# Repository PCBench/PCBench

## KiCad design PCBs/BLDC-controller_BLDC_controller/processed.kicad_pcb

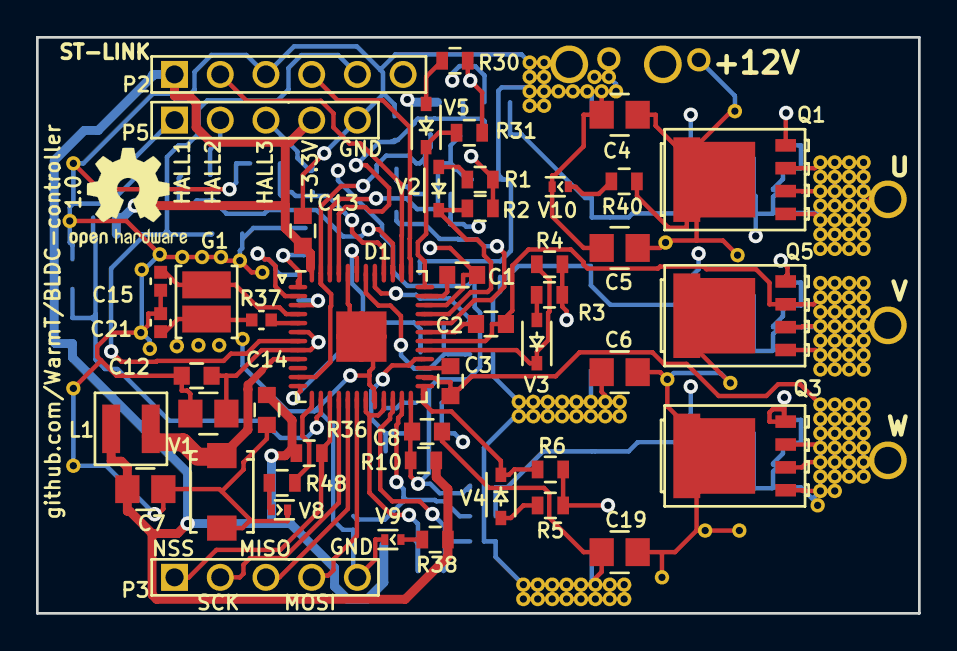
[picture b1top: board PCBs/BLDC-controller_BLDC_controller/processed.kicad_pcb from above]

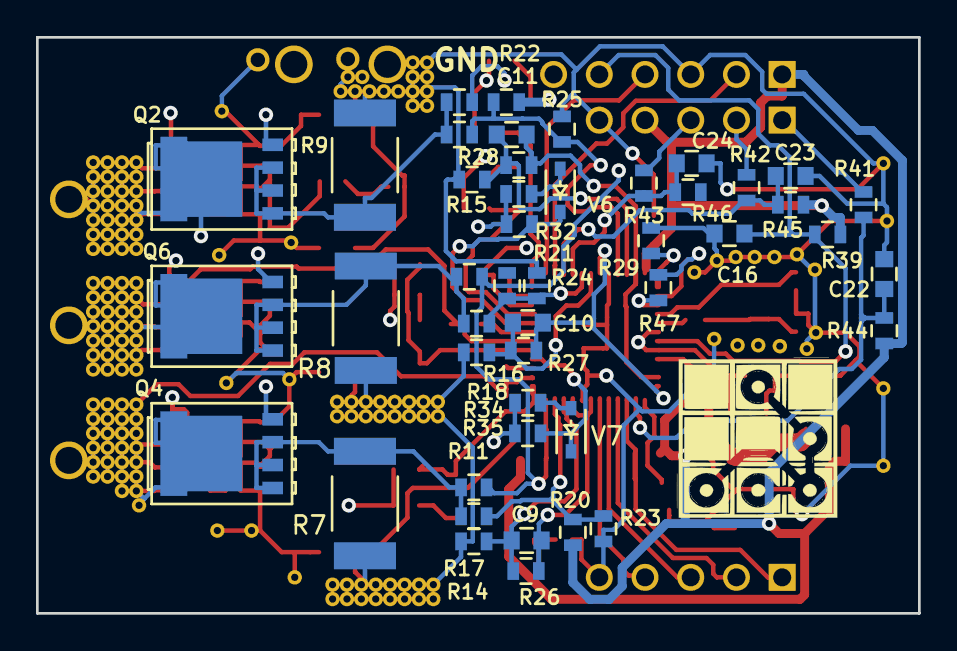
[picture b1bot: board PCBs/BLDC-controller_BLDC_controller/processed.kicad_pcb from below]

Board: 4 copper layers, 49.0 x 32.0 mm, 92 parts (46 on the bottom side), 64 nets.

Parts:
C1, C2, C3, C12, C13, C14: 100n; C_0603
C4, C5, C6, C17, C19: 220n; C_0805
C7: 47u; C_0805
C8: 1n0; C_0603
C9, C10, C11: 100p; C_0603
C15, C21: 10p; C_0402
C16: 3n3; C_0603
C22, C23, C24: 10p; C_0603
D1: STSPIN32F0; QFN-48-1EP_7x7mm_Pitch0.5mm
G1: NX3225GD; Crystal_3225
L1: SRN3015-220M; BOURNS-SRN3015
P2: CONN_01X06; PINHEAD1-6
P3, P5: CONN_01X05; PINHEAD1-5
Q1, Q2, Q3, Q4, Q5, Q6: PSMN2R0-30YLD; SOT-669_LFPAK56
R1, R3, R5, R30, R32, R34, R47: 10R; R_0603
R2, R4, R6, R31, R33, R35: 62R; R_0603
R7, R8, R9: 0R01; R_2512
R10: 46k4; R_0603
R11, R12, R13, R29, R36, R40: 2k2; R_0603
R14, R15, R16, R41, R42, R43: 1k0; R_0603
R17, R18, R19, R23, R24, R25, R48: 560R; R_0603
R20, R21, R22: 8k2; R_0603
R26, R27, R28: 15k; R_0603
R37: 10R; R_0402_MOST
R38: 330R; R_0603
R39: 39k; R_0603
R44, R45, R46: 10k; R_0603
V1: STPS1L60A; SMA
V2, V3, V4, V5, V6, V7: 4148WS; SOD-323
V8, V9, V10: LED_ALT; LED_0402

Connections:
+3V3: C7.1, C13.1, C14.1, D1.48, L1.1, P2.1, P5.4, R10.2, R20.1, R22.1, R36.1, R38.1, R39.1, R44.1, R45.1
+12V: C4.1, C5.1, C6.1, C12.1, C17.1, C19.1, D1.6, D1.8, Q1.5, Q3.5, Q5.5, R40.1
/HALL1/A+: C22.1, D1.14, R41.1, R44.2
/HALL2/B+: C23.1, D1.39, R42.1, R45.2
/HALL3/Z+: C24.1, D1.40, R43.1, R46.2
/HSU: Q1.4, R1.1, R2.1
/HSV: Q5.4, R3.1, R4.1
/HSW: Q3.4, R5.1, R6.1
/LSU: Q2.4, R30.1, R31.1
/LSV: Q6.4, R32.1, R33.1
/LSW: Q4.4, R34.1, R35.1
/NRST: C16.1, D1.7, P2.5, R39.2
/OC_COMP: C8.1, D1.24, R10.1, R11.2, R12.2, R13.2
/OP1N: C9.2, D1.22, R14.2, R26.2
/OP1P: D1.23, R17.1, R20.2, R23.1
/OP2N: C10.2, D1.42, R16.2, R27.2
/OP2P: D1.41, R18.1, R21.2, R24.1
/OP3N: C11.2, D1.46, R15.2, R28.2
/OP3P: D1.45, R19.1, R22.2, R25.1
/OP4N: D1.2, R47.2
/OP4P: D1.1, R29.1
/OSC_IN: C15.1, D1.4, G1.1
/OUTU: C1.1, D1.34, Q1.1, Q1.2, Q1.3, Q2.5
/OUTV: C2.1, D1.30, Q5.1, Q5.2, Q5.3, Q6.5
/OUTW: C3.1, D1.26, Q3.1, Q3.2, Q3.3, Q4.5
/PA2: D1.13, R48.1
/PA2_LED: R48.2, V8.2
/SPI1_MISO: D1.17, P3.3
/SPI1_MOSI: D1.18, P3.4
/SPI1_NSS: D1.15, P3.1, R36.2
/SPI1_SCK: D1.16, P3.2
/SW: D1.9, L1.2, V1.1
/SWCLK: D1.38, P2.2
/SWDIO: D1.37, P2.4
/U_ADC: C11.1, D1.11, D1.47, R28.1
/VBOOSTU: C1.2, D1.35
/VBOOSTV: C2.2, D1.31
/VBOOSTW: C3.2, D1.27
/V_ADC: C10.1, D1.12, D1.43, R27.1
/W_ADC: C9.1, D1.19, D1.21, R26.1
GND: C4.2, C5.2, C6.2, C7.2, C8.2, C12.2, C13.2, C14.2, C15.2, C16.2, C17.2, C19.2, C21.2, C22.2, C23.2, C24.2, D1.20, D1.44, D1.49, P2.3, P3.5, P5.5, R7.2, R8.2, R9.2, R14.1, R15.1, R16.1, R23.2, R24.2, R25.2, R29.2, V1.2, V8.1, V9.1, V10.1
unnamed: C21.1, G1.2, R37.2
unnamed: D1.3, R47.1
unnamed: D1.5, R37.1
unnamed: D1.25, R6.2, V4.1
unnamed: D1.28, R35.2, V7.1
unnamed: D1.29, R4.2, V3.1
unnamed: D1.32, R33.2, V6.1
unnamed: D1.33, R2.2, V2.1
unnamed: D1.36, R31.2, V5.1
unnamed: P5.1, R41.2
unnamed: P5.2, R42.2
unnamed: P5.3, R43.2
unnamed: R1.2, V2.2
unnamed: R3.2, V3.2
unnamed: R5.2, V4.2
unnamed: R30.2, V5.2
unnamed: R32.2, V6.2
unnamed: R34.2, V7.2
unnamed: R38.2, V9.2
unnamed: R40.2, V10.2
U_SENSE_P: Q2.1, Q2.2, Q2.3, R9.1, R13.1, R19.2
V_SENSE_P: Q6.1, Q6.2, Q6.3, R8.1, R12.1, R18.2
W_SENSE_P: Q4.1, Q4.2, Q4.3, R7.1, R11.1, R17.2

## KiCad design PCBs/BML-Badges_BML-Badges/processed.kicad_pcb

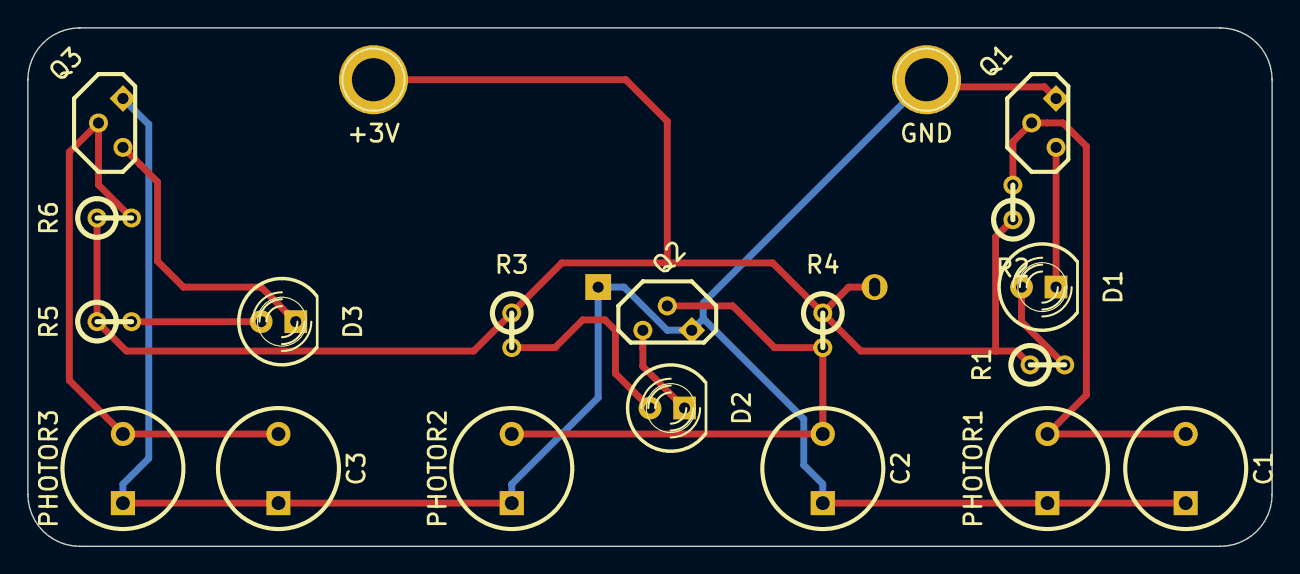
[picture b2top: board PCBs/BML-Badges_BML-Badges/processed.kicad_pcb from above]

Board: 2 copper layers, 91.4 x 38.1 mm, 21 parts (1 on the bottom side), 11 nets.

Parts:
BT1: 3V; BS-7-CR2032-2
C1, C2, C3: 22uF; C2V8
D1, D2, D3: LED; LED-5MM
P1: +3V; 1pin
P2: GND; 1pin
PHOTOR1, PHOTOR2, PHOTOR3: PHOTOR; LDR
Q1, Q2, Q3: PN2222A; TO92-EBC-num
R1, R3, R5: 330; R1
R2, R4, R6: 100k; R1

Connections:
3V: BT1.1, P1.1, R1.1, R2.1, R3.1, R4.1, R5.1, R6.1
GND: BT1.2, C1.2, C2.2, C3.2, P2.1, PHOTOR1.2, PHOTOR2.2, PHOTOR3.2, Q1.1, Q2.1, Q3.1
unnamed: C1.1, PHOTOR1.1, Q1.2, R2.2
unnamed: C2.1, PHOTOR2.1, Q2.2, R4.2
unnamed: C3.1, PHOTOR3.1, Q3.2, R6.2
unnamed: D1.1, R1.2
unnamed: D1.2, Q1.3
unnamed: D2.1, R3.2
unnamed: D2.2, Q2.3
unnamed: D3.1, R5.2
unnamed: D3.2, Q3.3

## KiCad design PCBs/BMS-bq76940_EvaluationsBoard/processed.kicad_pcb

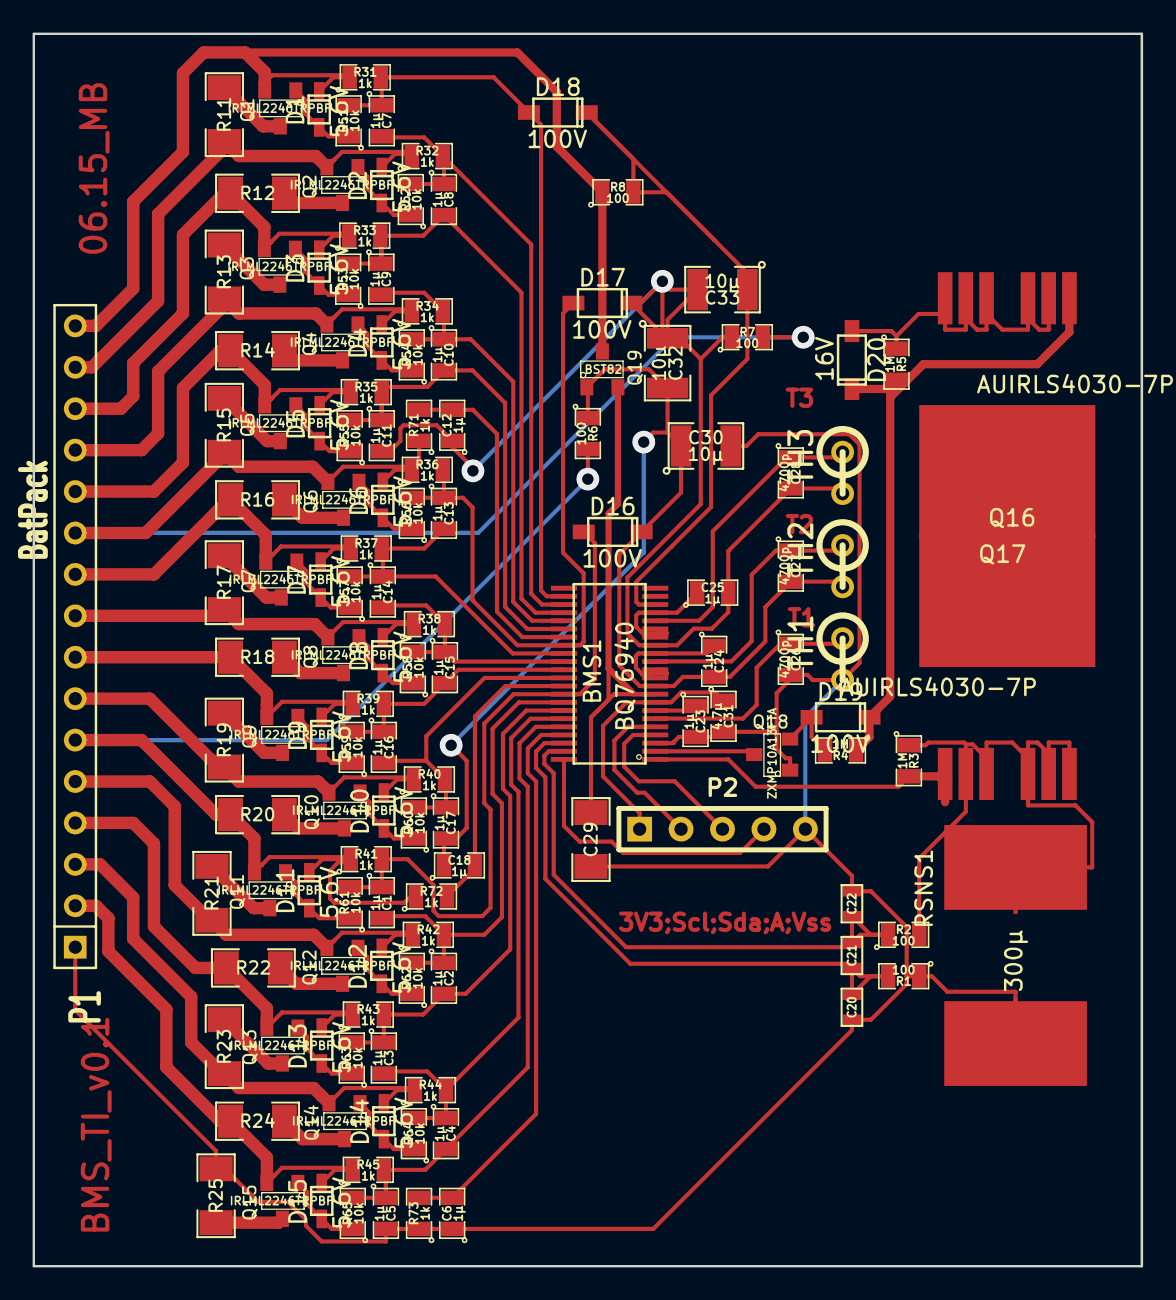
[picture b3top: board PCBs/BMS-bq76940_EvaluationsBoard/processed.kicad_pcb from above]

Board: 2 copper layers, 67.9 x 75.6 mm, 134 parts (0 on the bottom side), 87 nets.

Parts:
BMS1: BQ76940
C1, C2, C3, C4, C5, C6, C7, C8, C9, C10, C11, C12, C13, C14, C15, C16, C17, C18, C23, C24, C25: 1µ; SM0805
C20, C21, C22: 0.1µ; SM0603
C26, C27, C28: 4700p; SM0805
C29: 1µ; SM1206
C30, C32, C33: 10µ; SM1210
C31: 4.7µ; SM0805
D1, D2, D3, D4, D5, D6, D7, D8, D9, D10, D11, D12, D13, D14, D15: 5.6V; SOD323
D16, D17, D18, D19: 100V; SOD123
D20: 16V; SOD123
P1: BatPack; SIL-16
P2: µC; PIN_ARRAY_5x1
Q1, Q2, Q3, Q4, Q5, Q6, Q7, Q8, Q9, Q10, Q11, Q12, Q13, Q14, Q15: IRLML2246TRPBF; SOT23
Q16, Q17: AUIRLS4030-7P
Q18: ZXMP10A13FTA; SOT23
Q19: BST82; SOT23
R1, R2, R6, R7, R8: 100; SM0805
R3, R4, R5: 1M; SM0805
R11, R12, R13, R14, R15, R16, R17, R18, R19, R20, R21, R22, R23, R24, R25: 39; SM1206
R31, R32, R33, R34, R35, R36, R37, R38, R39, R40, R41, R42, R43, R44, R45, R71, R72, R73: 1k; SM0805
R51, R52, R53, R54, R55, R56, R57, R58, R59, R60, R61, R62, R63, R64, R65: 10k; SM0805
RSNS1: 300µ; WSLP5931
TH1, TH2, TH3: THERMISTOR; R1

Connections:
/BatPack/C1: D15.2, P1.2, Q15.2, R24.1, R45.1
/BatPack/C2: D14.2, P1.3, Q14.2, R23.1, R44.1
/BatPack/C3: D13.2, P1.4, Q13.2, R22.1, R43.1
/BatPack/C4: D12.2, P1.5, Q12.2, R21.1, R42.1
/BatPack/C6: D10.2, P1.7, Q10.2, R19.1, R40.1
/BatPack/C7: D9.2, P1.8, Q9.2, R18.1, R39.1
/BatPack/C8: D8.2, P1.9, Q8.2, R17.1, R38.1
/BatPack/C9: D7.2, P1.10, Q7.2, R16.1, R37.1
/BatPack/C11: D5.2, P1.12, Q5.2, R14.1, R35.1
/BatPack/C12: D4.2, P1.13, Q4.2, R13.1, R34.1
/BatPack/C13: D3.2, P1.14, Q3.2, R12.1, R33.1
/BatPack/C14: D2.2, P1.15, Q2.2, R11.1, R32.1
/BatPack/VC0: BMS1.41, C6.2, R73.2
/BatPack/VC1: BMS1.40, C4.2, C5.1, R45.2, R65.2
/BatPack/VC2: BMS1.39, C3.2, C4.1, R44.2, R64.2
/BatPack/VC3: BMS1.38, C2.2, C3.1, R43.2, R63.2
/BatPack/VC4: BMS1.37, C1.2, C2.1, R42.2, R62.2
/BatPack/VC5: BMS1.36, C1.1, D16.1, R41.2, R61.2
/BatPack/VC6: BMS1.34, C16.2, C17.1, R40.2, R60.2
/BatPack/VC7: BMS1.33, C15.2, C16.1, R39.2, R59.2
/BatPack/VC8: BMS1.32, C14.2, C15.1, R38.2, R58.2
/BatPack/VC9: BMS1.31, C13.2, C14.1, R37.2, R57.2
/BatPack/VC10: BMS1.30, C13.1, D17.1, R36.2, R56.2
/BatPack/VC11: BMS1.28, C10.2, C11.1, R35.2, R55.2
/BatPack/VC12: BMS1.27, C9.2, C10.1, R34.2, R54.2
/BatPack/VC13: BMS1.26, C8.2, C9.1, R33.2, R53.2
/BatPack/VC14: BMS1.25, C7.2, C8.1, R32.2, R52.2
/BatPack/VC15: BMS1.24, C7.1, D18.1, R31.2, R51.2
/COM/BAT: BMS1.20, C33.1, D18.2, R8.2
/COM/CHG: BMS1.2, Q18.3
/COM/DSC: BMS1.1, Q16.1, R3.2
/COM/REGOUT: BMS1.8, C31.1, P2.1
/COM/REGSRC: BMS1.9, C29.1, Q19.2
/COM/SCL: BMS1.5, P2.2
/COM/SDA: BMS1.4, P2.3
/COM/SRN: BMS1.43, C21.2, C22.1, R2.1
/COM/SRP: BMS1.42, C20.2, C21.1, R1.2
A: D11.2, P1.6, Q11.2, R6.2, R20.1, R41.1, R72.1
ALERT: BMS1.44, P2.4
B: D6.2, P1.11, Q6.2, R7.2, R15.1, R36.1, R71.1
unnamed: D5.1, Q5.1, R55.1
unnamed: D3.1, Q3.1, R53.1
unnamed: D4.1, Q4.1, R54.1
unnamed: D6.1, Q6.1, R56.1
unnamed: D2.1, Q2.1, R52.1
unnamed: D1.1, Q1.1, R51.1
unnamed: Q3.3, R13.2
unnamed: Q4.3, R14.2
unnamed: Q5.3, R15.2
unnamed: Q6.3, R16.2
unnamed: Q7.3, R17.2
unnamed: Q8.3, R18.2
unnamed: D9.1, Q9.1, R59.1
unnamed: Q9.3, R19.2
unnamed: D10.1, Q10.1, R60.1
unnamed: Q1.3, R11.2
unnamed: Q2.3, R12.2
unnamed: Q14.3, R24.2
unnamed: Q13.3, R23.2
unnamed: Q12.3, R22.2
unnamed: Q11.3, R21.2
unnamed: Q10.3, R20.2
unnamed: Q15.3, R25.2
unnamed: D11.1, Q11.1, R61.1
unnamed: D12.1, Q12.1, R62.1
unnamed: D14.1, Q14.1, R64.1
unnamed: D7.1, Q7.1, R57.1
unnamed: D8.1, Q8.1, R58.1
unnamed: D13.1, Q13.1, R63.1
unnamed: D15.1, Q15.1, R65.1
unnamed: BMS1.7, C23.1
unnamed: BMS1.16, BMS1.17, BMS1.19, C25.1
unnamed: BMS1.11, BMS1.12, BMS1.14, C24.1
unnamed: D19.2, D20.2, Q17.1, R4.1, R5.2
unnamed: Q16.8, Q17.8
unnamed: D19.1, Q18.2, R4.2
unnamed: Q16.2, Q16.3, Q16.5, Q16.6, Q16.7, R2.2, R3.1, RSNS1.1
PACK+: D1.2, P1.16, Q1.2, Q19.3, R8.1, R31.1
PACK-: D20.1, Q17.2, Q17.3, Q17.5, Q17.6, Q17.7, R5.1
TS1: BMS1.6, C26.1, TH1.1
TS2: BMS1.13, C27.1, TH2.1
TS3: BMS1.18, C28.1, TH3.1
VC5B: BMS1.35, C18.2, R72.2
VC5x: BMS1.10, C17.2, C18.1, C24.2, C27.2, C30.1, C32.2, D16.2, Q19.1, R6.1, TH2.2
VC10B: BMS1.29, C12.2, R71.2
VC10x: BMS1.15, C11.2, C12.1, C25.2, C28.2, C32.1, C33.2, D17.2, R7.1, TH3.2
VSS: BMS1.3, C5.2, C6.1, C20.1, C22.2, C23.2, C26.2, C29.2, C30.2, C31.2, P1.1, P2.5, Q18.1, R1.1, R25.1, R73.1, RSNS1.2, TH1.2

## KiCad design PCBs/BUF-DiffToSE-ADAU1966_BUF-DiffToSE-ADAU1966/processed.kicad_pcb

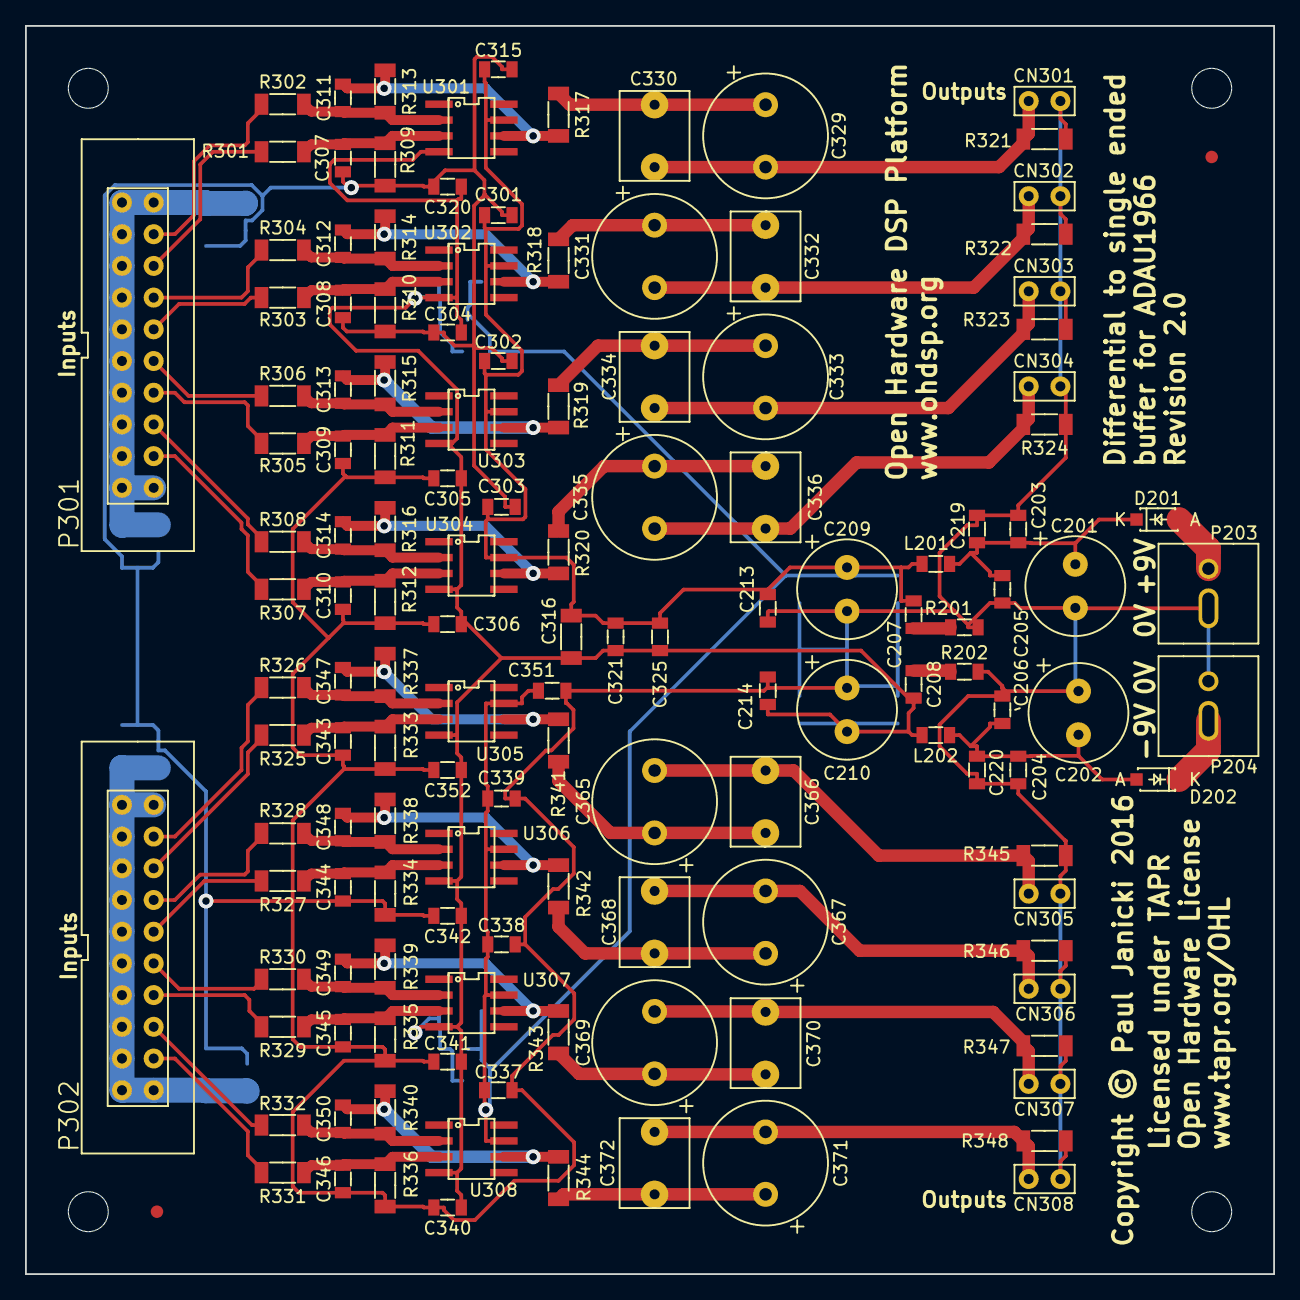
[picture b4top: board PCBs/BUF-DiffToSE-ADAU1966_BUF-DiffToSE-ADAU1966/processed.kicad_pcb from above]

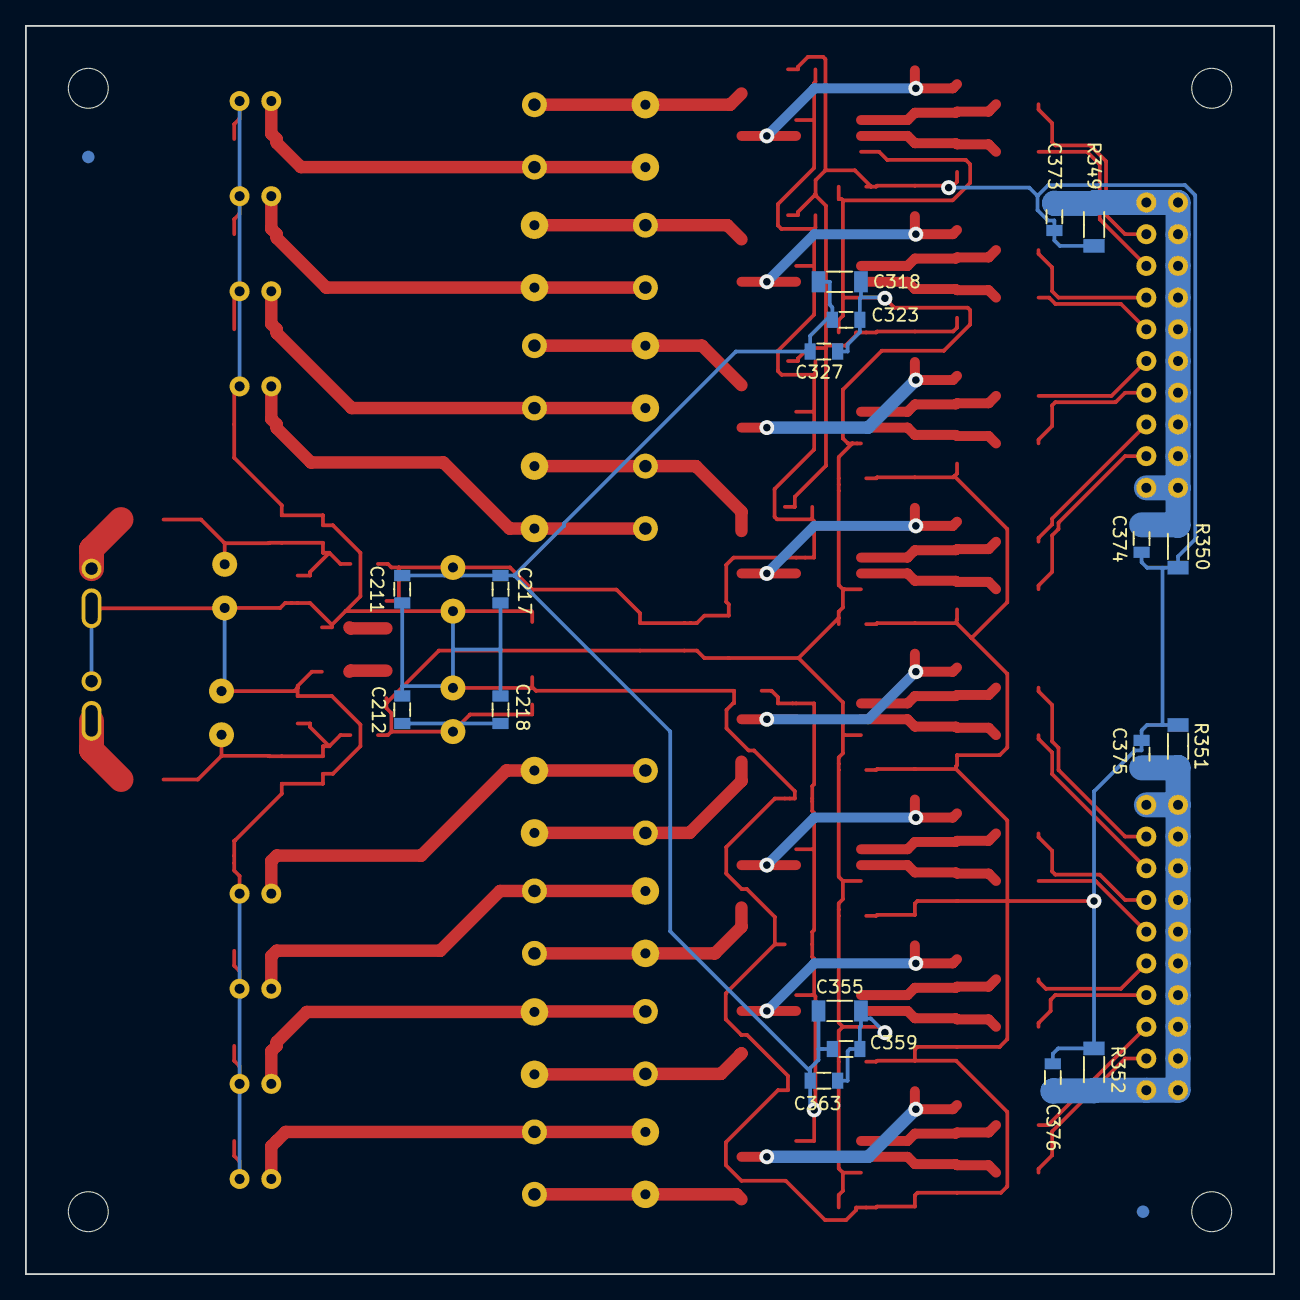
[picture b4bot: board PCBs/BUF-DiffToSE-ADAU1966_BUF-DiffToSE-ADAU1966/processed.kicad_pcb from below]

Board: 2 copper layers, 100.0 x 100.0 mm, 165 parts (20 on the bottom side), 67 nets.

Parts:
C201, C202, C209, C210: 220u; CAP-TH-D8mmP3.5mm
C203, C204, C211, C212, C301, C302, C303, C304, C305, C306, C315, C320, C321, C323, C337, C338, C339, C340, C341, C342, C351, C352, C359, C373, C374, C375, C376: 100n; SMD-0805
C205, C206, C213, C214, C325, C327, C363: 10n; SMD-0805
C207, C208: 100p; SMD-0805
C217, C218, C219, C220: 22u; SMD-0805
C307, C308, C309, C310, C311, C312, C313, C314, C343, C344, C345, C346, C347, C348, C349, C350: 1n; SMD-0805
C316, C318, C355: 10u; SMD-1206
C329, C331, C333, C335, C365, C367, C369, C371: 100u; CAP-TH-D10mmP5mm
C330, C332, C334, C336, C366, C368, C370, C372: 100n; CAP_TH_5mm
CN301, CN302, CN303, CN304, CN305, CN306, CN307, CN308: COAX; CONN_SIL_2
D201, D202: SS14L; DIODE-SOD-123
FID1, FID2, FID3, FID4: MNT_HOLE; FID-1MM-3MM
L201, L202: 600R@100MHz; SMD-0805
MNT201, MNT202, MNT203, MNT204: MNT_HOLE; MNT_HOLE_3.2mm
P203, P204: CONN_2x1; CONN-2WAY-2.54mm-3.81mm-SPACING
P301, P302: CONN_02X10; CONN_DIL_2X10_BOX
R201, R202: 47; SMD-0805
R301, R302, R303, R304, R305, R306, R307, R308, R325, R326, R327, R328, R329, R330, R331, R332: 1k3; SMD-1206
R309, R310, R311, R312, R313, R314, R315, R316, R333, R334, R335, R336, R337, R338, R339, R340: 1k5; SMD-1206
R317, R318, R319, R320, R341, R342, R343, R344: 100; SMD-1206
R321, R322, R323, R324, R345, R346, R347, R348: 100k; SMD-1206
R349, R350, R351, R352: 10; SMD-1206
U301, U302, U303, U304, U305, U306, U307, U308: TLE2071; IC_SOIC_8

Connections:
+9VA: C207.1, C209.1, C211.1, C213.1, C217.1, C301.1, C302.1, C303.1, C315.1, C316.1, C318.1, C321.1, C323.1, C325.1, C327.1, C337.1, C338.1, C339.1, C351.1, C355.1, C359.1, C363.1, L201.2, U301.7, U302.7, U303.7, U304.7, U305.7, U306.7, U307.7, U308.7
-9VA: C208.2, C210.2, C212.2, C214.2, C218.2, C304.2, C305.2, C306.2, C316.2, C318.2, C320.2, C321.2, C323.2, C325.2, C327.2, C340.2, C341.2, C342.2, C352.2, C355.2, C359.2, C363.2, L202.2, U301.4, U302.4, U303.4, U304.4, U305.4, U306.4, U307.4, U308.4
GNDA: C201.2, C202.1, C203.2, C204.1, C205.2, C206.1, C209.2, C210.1, C211.2, C212.1, C213.2, C214.1, C217.2, C218.1, C219.2, C220.1, C301.2, C302.2, C303.2, C304.1, C305.1, C306.1, C307.2, C308.2, C309.2, C310.2, C315.2, C320.1, C337.2, C338.2, C339.2, C340.1, C341.1, C342.1, C343.2, C344.2, C345.2, C346.2, C351.2, C352.1, C373.2, C374.2, C375.2, C376.2, CN301.2, CN302.2, CN303.2, CN304.2, CN305.2, CN306.2, CN307.2, CN308.2, P203.2, P204.1, R201.2, R202.1, R309.1, R310.1, R311.1, R312.1, R321.1, R322.1, R323.1, R324.1, R333.1, R334.1, R335.1, R336.1, R345.1, R346.1, R347.1, R348.1, R349.1, R350.1, R351.1, R352.1
unnamed: C201.1, C203.1, C205.1, C219.1, D201.2, L201.1
unnamed: C202.2, C204.2, C206.2, C220.2, D202.1, L202.1
unnamed: C207.2, R201.1
unnamed: C208.1, R202.2
unnamed: C307.1, R301.1, R309.2, U301.3
unnamed: C308.1, R303.1, R310.2, U302.3
unnamed: C309.1, R305.1, R311.2, U303.3
unnamed: C310.1, R307.1, R312.2, U304.3
unnamed: C311.1, R302.1, R313.2, U301.2
unnamed: C311.2, R313.1, R317.2, U301.6
unnamed: C312.1, R304.1, R314.2, U302.2
unnamed: C312.2, R314.1, R318.2, U302.6
unnamed: C313.1, R306.1, R315.2, U303.2
unnamed: C313.2, R315.1, R319.2, U303.6
unnamed: C314.1, R308.1, R316.2, U304.2
unnamed: C314.2, R316.1, R320.2, U304.6
unnamed: C329.1, C330.1, R317.1
unnamed: C329.2, C330.2, CN301.1, R321.2
unnamed: C331.1, C332.1, R318.1
unnamed: C331.2, C332.2, CN302.1, R322.2
unnamed: C333.1, C334.1, R319.1
unnamed: C333.2, C334.2, CN303.1, R323.2
unnamed: C335.1, C336.1, R320.1
unnamed: C335.2, C336.2, CN304.1, R324.2
unnamed: C343.1, R325.1, R333.2, U305.3
unnamed: C344.1, R327.1, R334.2, U306.3
unnamed: C345.1, R329.1, R335.2, U307.3
unnamed: C346.1, R331.1, R336.2, U308.3
unnamed: C347.1, R326.1, R337.2, U305.2
unnamed: C347.2, R337.1, R341.2, U305.6
unnamed: C348.1, R328.1, R338.2, U306.2
unnamed: C348.2, R338.1, R342.2, U306.6
unnamed: C349.1, R330.1, R339.2, U307.2
unnamed: C349.2, R339.1, R343.2, U307.6
unnamed: C350.1, R332.1, R340.2, U308.2
unnamed: C350.2, R340.1, R344.2, U308.6
unnamed: C365.1, C366.1, R341.1
unnamed: C365.2, C366.2, CN305.1, R345.2
unnamed: C367.1, C368.1, R342.1
unnamed: C367.2, C368.2, CN306.1, R346.2
unnamed: C369.1, C370.1, R343.1
unnamed: C369.2, C370.2, CN307.1, R347.2
unnamed: C371.1, C372.1, R344.1
unnamed: C371.2, C372.2, CN308.1, R348.2
unnamed: C373.1, C374.1, P301.1, P301.2, P301.3, P301.5, P301.7, P301.9, P301.11, P301.13, P301.15, P301.17, P301.19, P301.20, R349.2, R350.2
unnamed: C375.1, C376.1, P302.1, P302.2, P302.3, P302.5, P302.7, P302.9, P302.11, P302.13, P302.15, P302.17, P302.19, P302.20, R351.2, R352.2
unnamed: D201.1, P203.1
unnamed: D202.2, P204.2
unnamed: P301.4, R302.2
unnamed: P301.6, R301.2
unnamed: P301.8, R304.2
unnamed: P301.10, R303.2
unnamed: P301.12, R306.2
unnamed: P301.14, R305.2
unnamed: P301.16, R308.2
unnamed: P301.18, R307.2
unnamed: P302.4, R326.2
unnamed: P302.6, R325.2
unnamed: P302.8, R328.2
unnamed: P302.10, R327.2
unnamed: P302.12, R330.2
unnamed: P302.14, R329.2
unnamed: P302.16, R332.2
unnamed: P302.18, R331.2

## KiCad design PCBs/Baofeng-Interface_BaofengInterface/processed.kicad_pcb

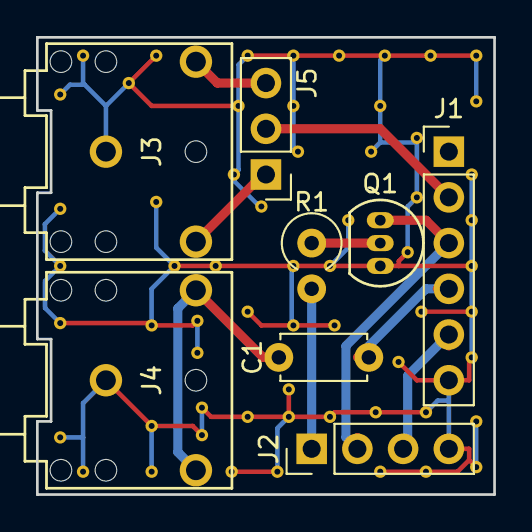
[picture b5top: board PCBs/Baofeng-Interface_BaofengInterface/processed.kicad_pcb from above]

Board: 2 copper layers, 25.4 x 25.4 mm, 8 parts (0 on the bottom side), 10 nets.

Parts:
C1: 1uF; C_Disc_D4.7mm_W2.5mm_P5.00mm
J1: CONN_01X06; Pin_Header_Straight_1x06_Pitch2.54mm
J2: CONN_01X04; Pin_Header_Straight_1x04_Pitch2.54mm
J3, J4: JACK_TRS_3PINS; SJ1-352XN
J5: CONN_01X03; Pin_Header_Straight_1x03_Pitch2.54mm
Q1: Q_NPN_CBE; TO-92_Inline_Narrow_Oval
R1: 1k; R_Axial_DIN0309_L9.0mm_D3.2mm_P2.54mm_Vertical

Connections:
GND: J1.6, J2.4, J3.1, J4.1, Q1.3
unnamed: C1.1, J4.2, J4.3
unnamed: Q1.2, R1.1
PTT: J2.1, R1.2
RX_AUDIO: C1.2, J1.4
SERIAL_RX: J1.3, J2.2, Q1.1
SERIAL_TX: J1.5, J2.3
TX_AUDIO: J1.2, J5.2
TX_LEFT+: J3.3, J5.3
TX_RIGHT+: J3.2, J5.1

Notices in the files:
PCBs/BUF-DiffToSE-ADAU1966_BUF-DiffToSE-ADAU1966/processed.kicad_pcb:
Licensed under the TAPR Open Hardware License (www.tapr.org/OHL). This documentation
Copyright Paul Janicki 2016
Copyright © Paul Janicki 2016
Licensed under TAPR
